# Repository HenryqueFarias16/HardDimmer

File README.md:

# HardDimmer
Automação Dimmerizada com microcontrolador ESP12-E

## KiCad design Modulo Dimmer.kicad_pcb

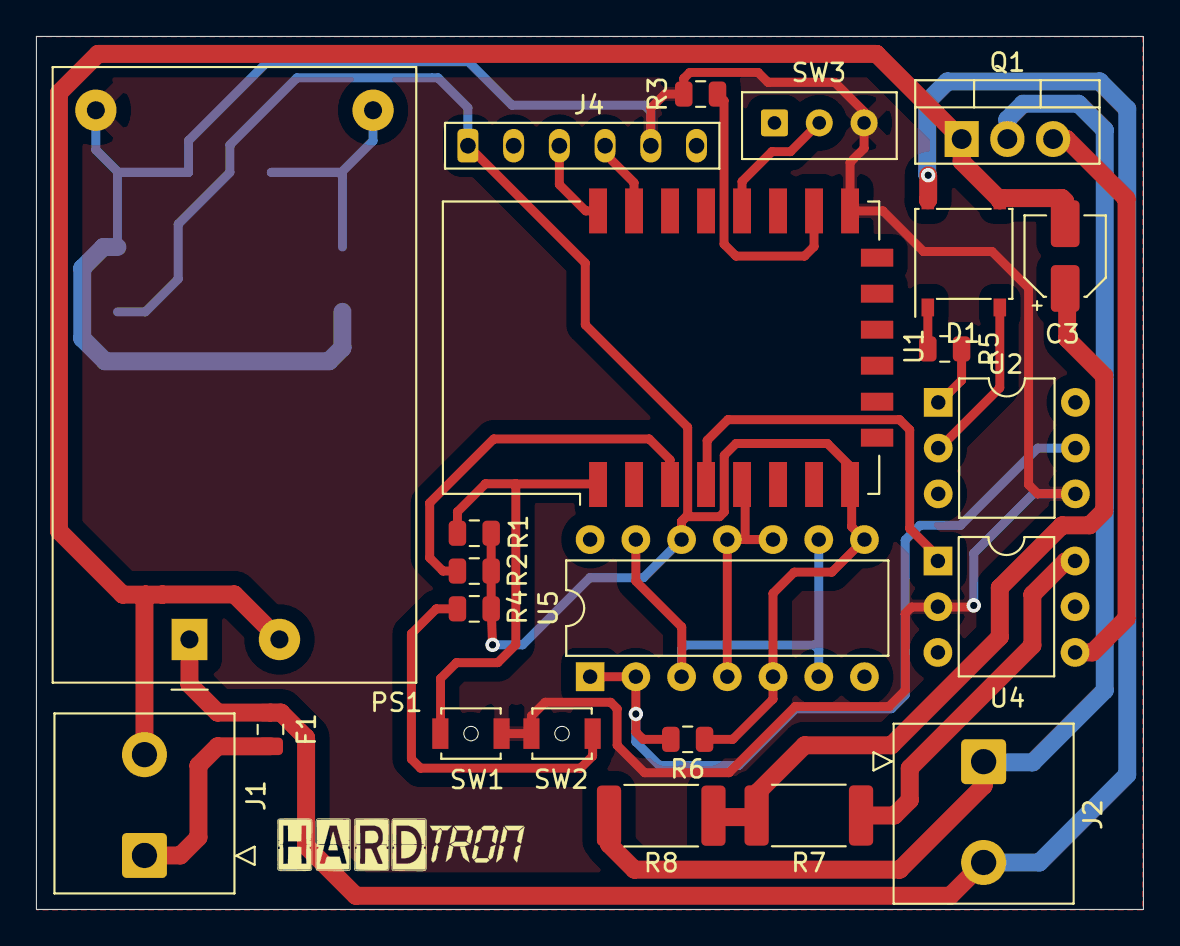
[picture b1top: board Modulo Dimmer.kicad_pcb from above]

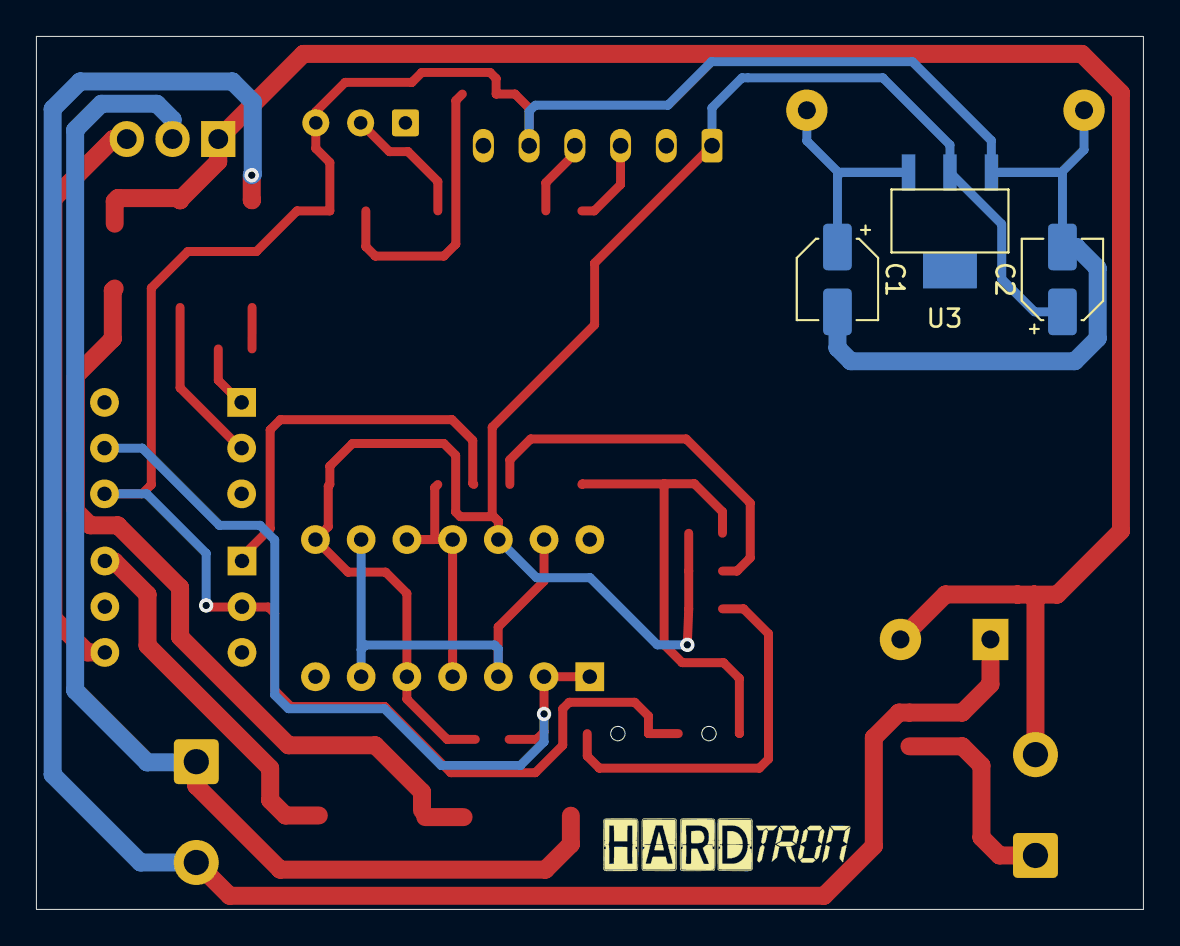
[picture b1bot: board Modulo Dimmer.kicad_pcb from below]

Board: 2 copper layers, 61.5 x 48.5 mm, 26 parts (3 on the bottom side), 24 nets.

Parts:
C1, C2, C3: 10uF; CP_Elec_4x5.4
D1: MBL106S; Diode_Bridge_Vishay_MBLS
F1: 1A; Fuse_0805_2012Metric
J1, J2: 300V/10A; Tblock10x10mm
J4: Cp2102; Wuerth_WR-WTB_64800611622_1x06_P2.50mm_Vertical
PS1: HLK-PM01; Converter_ACDC_HiLink_HLK-PMxx
Q1: BT136-600; TO-220-3_Vertical
R1, R2, R3, R4, R6: 10k; R_0805_2012Metric
R5: 1k; R_0805_2012Metric
R7: 200; R_2512_6332Metric
R8: 2.7k; R_2512_6332Metric
SW1, SW2: B3U-1000P-B; SW_SPST_B3U-1000P-B
SW3: SS12D00; TE_826576-3_1x03_P1mm_Vertical
U1: ESP-12E
U2: 4N25; DIP-6_W7.62mm
U3: LM1117-3.3; R-PDSO-G4
U4: MOC3020M; DIP-6_W7.62mm
U5: 4093; DIP-14_W7.62mm

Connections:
+3V3: C2.1, J4.1, R1.2, R2.2, R4.2, R6.1, U1.8, U3.2, U5.5, U5.8, U5.12
EN: R2.1, U1.3
Fase: F1.1, J1.1
Fusivel: D1.4, F1.2, J2.2, PS1.1
GND: C1.2, C2.2, J4.5, PS1.3, R3.1, SW1.2, SW2.2, SW3.3, U1.15, U2.4, U3.1, U4.2
Gpio0: SW3.2, U1.18
Gpio15: R3.2, U1.16
Gpio16: R4.1, SW2.1
InputZeroCrossing: U1.5, U5.4, U5.10, U5.11
unnamed: C1.1, PS1.4, U3.3
unnamed: C3.1, R7.2, R8.1
unnamed: D1.1, R5.1
unnamed: D1.2, U2.2
unnamed: J2.1, Q1.2, R8.2
unnamed: Q1.3, U4.4
unnamed: R5.2, U2.1
unnamed: R7.1, U4.6
unnamed: U5.3, U5.6, U5.9, U5.13
Neutro: C3.2, D1.3, J1.2, PS1.2, Q1.1
Rst: R1.1, SW1.1, U1.1
Rx: J4.4, U1.21
Triac_control: U1.4, U4.1
Tx: J4.3, U1.22
ZeroCrossing: R6.2, U2.5, U5.1, U5.2
